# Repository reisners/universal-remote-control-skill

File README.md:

# universal-remote-control-skill

This repository contains resources comprising the Universal Remote Control Alexa Skill

# High-Level Description of the Solution

The system consists of the following components:
* Global components:
  * Alexa Smart Home Skill
  * AWS Lambda function
  * AWS API Gateway websocket endpoint (backed by additional AWS Lambda functions to handle connections)
* Per user-components:
  * Google Account containing a Google Spreadsheet with a fixed name
  * Universal Remote Controller (URC) device based on an ESP8266 micro-controller

The Alexa Smart Home Skill is linked to the user's Google Account in order to access the spreadsheet.
When the user requests device discovery, the skill passes the discovery request on to the AWS Lambda function 
which in turn reads the rows from the spreadsheet and translates them into Alexa Smart Home Device metadata.
Each row contains
* URCID (a unique ID of the URC device derived from an on-board DS2401 chip)
* user-friendly name of the appliance to control, e.g. "Ceiling Fan"
* device category (as prescribed by Alexa Smart Home API)
* operation to perform on that device, e.g. TurnOn/TurnOff
* channel of communication with the appliance (infrared of 433MHz radio waves)
* data package to transmit to the appliance to effect the intended operation

The URC device upon startup creates a websocket connection to the AWS API Gateway via WiFi and passes on its unique URCID.
The AWS Lambda function handling websocket connections stores the combination of URCID and websocket connection ID in an
AWS Dynamo DB table.

When the user requests a device operation via voice command, the skill sends another request to the AWS Lambda function
which refers to the device metadata created during discovery. The AWS Lambda function uses the URCID to find an active
websocket connection ID in the AWS Dynamo DB table, deleting any stale connection IDs it finds. It then sends a message
to the URC device via that websocket connection. This message contains the chosen channel and data package from the Google spreadsheet.

The URC device listens on the open websocket connection for messages and transmits the data to the appliance via infrared or 433MHz radio waves.

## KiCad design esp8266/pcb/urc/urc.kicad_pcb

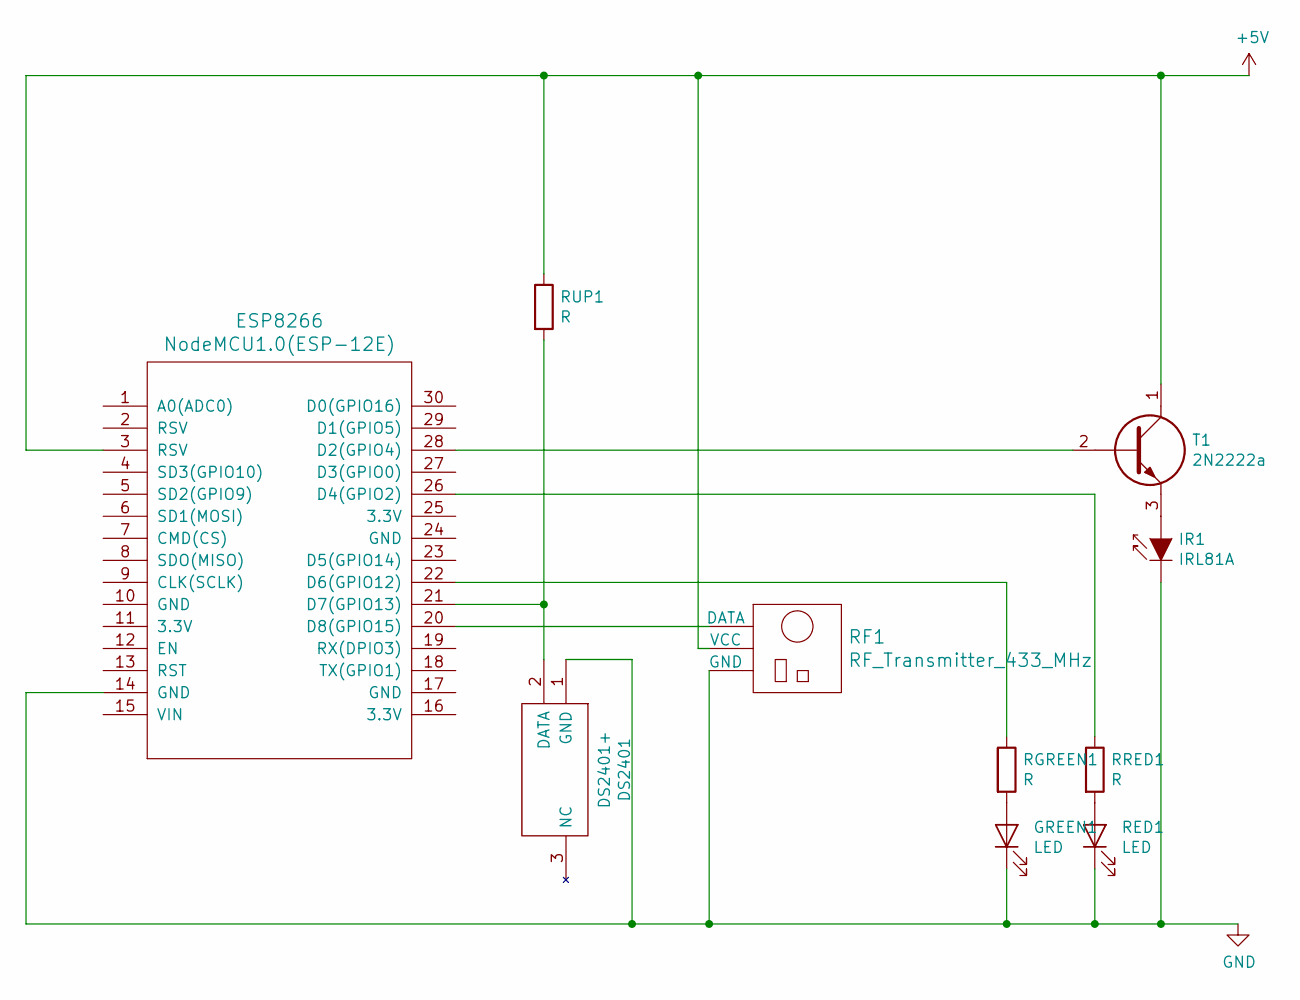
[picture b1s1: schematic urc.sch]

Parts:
DS2401: DS2401+; 2N6027
ESP8266: NodeMCU1.0(ESP-12E); NodeMCU-LoLinV3
GREEN1: LED; LED_D5.0mm
IR1: IRL81A; PinHeader_1x02_P1.00mm_Horizontal
RED1: LED; LED_D5.0mm
RF1: RF_Transmitter_433_MHz
RGREEN1: R; R_Axial_DIN0204_L3.6mm_D1.6mm_P2.54mm_Vertical
RRED1: R; R_Axial_DIN0204_L3.6mm_D1.6mm_P2.54mm_Vertical
RUP1: R; R_Axial_DIN0204_L3.6mm_D1.6mm_P2.54mm_Vertical
T1: 2N2222a; 2N6027

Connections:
+5V: ESP8266.3 (RSV), RF1.2 (VCC), RUP1.1, T1.1
GND: DS2401.1 (GND), ESP8266.14 (GND), GREEN1.1 (K), IR1.1 (K), RED1.1 (K), RF1.3 (GND)
unnamed: DS2401.2 (DATA), ESP8266.21 (D7(GPIO13)), RUP1.2
unnamed: ESP8266.20 (D8(GPIO15)), RF1.1 (DATA)
unnamed: ESP8266.22 (D6(GPIO12)), RGREEN1.1
unnamed: ESP8266.26 (D4(GPIO2)), RRED1.1
unnamed: ESP8266.28 (D2(GPIO4)), T1.2
unnamed: GREEN1.2 (A), RGREEN1.2
unnamed: IR1.2 (A), T1.3
unnamed: RED1.2 (A), RRED1.2

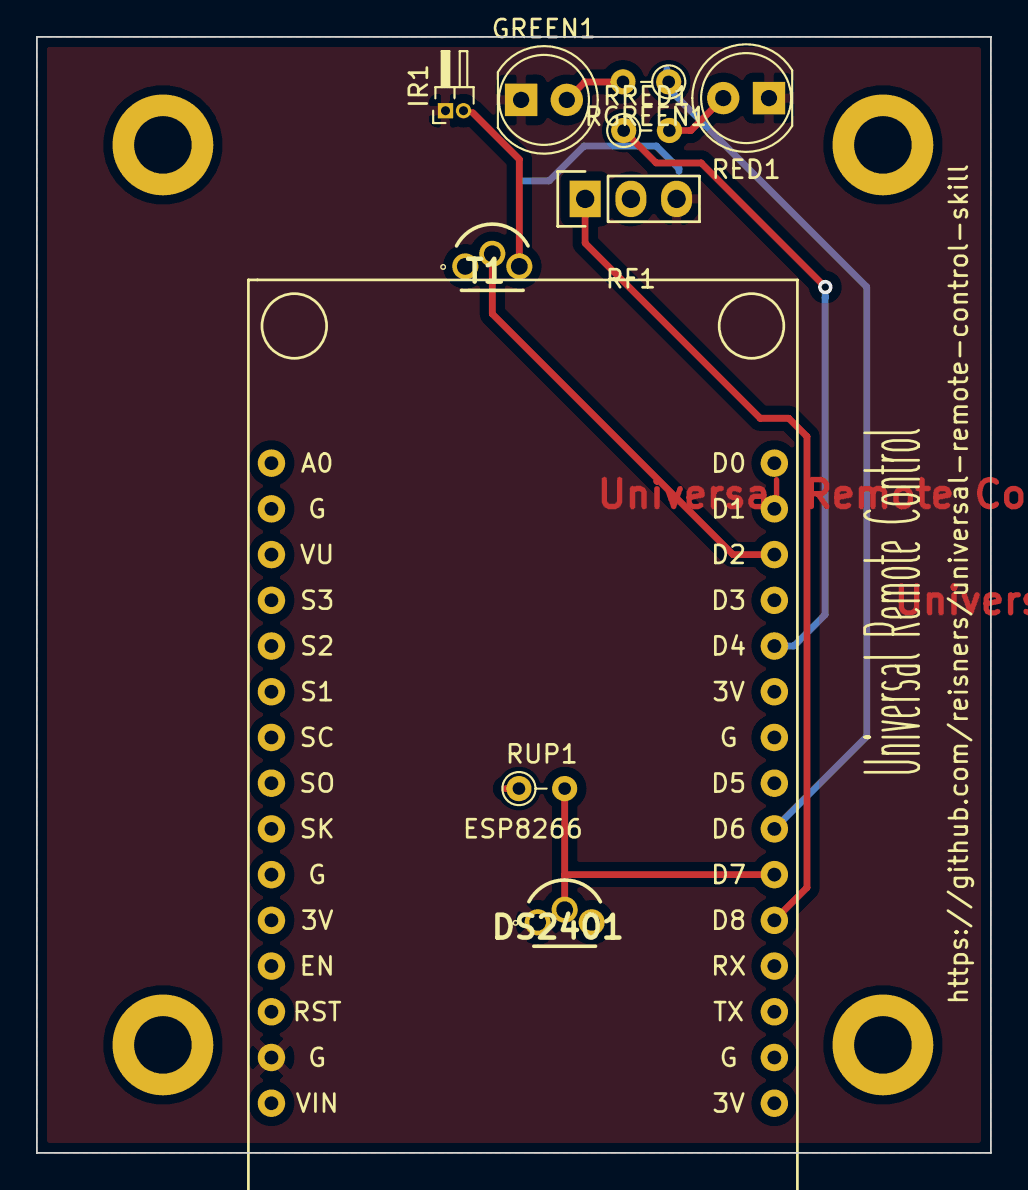
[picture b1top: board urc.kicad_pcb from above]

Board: 2 copper layers, 53.0 x 62.0 mm, 10 parts (0 on the bottom side), 10 nets.

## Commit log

2019-04-21 adr initialized
2019-08-27 renamed universion-remote-control-smart-home-skill (from universal-remote-control), added claudia.json, package-lock.json
2019-08-30 documentation updated
2019-08-30 image1.jpg added
2019-08-30 renamed esp8266/urc
2019-10-15 updated urc.ino: adding status LEDs
2019-10-20 updated lambda/universal-remote-control-smart-home-skill/index.js
2019-11-07 added emulator
2019-11-10 updated emulator.js
2019-11-10 updated urc.ino
2019-12-05 updated index.js: improving discovery error handling
2019-12-05 added esp8266/pcb
2020-06-08 updated index.js: logging
2020-06-08 updated urc.ino: improved LED signaling
2020-09-02 Bump googleapis in /lambda/universal-remote-control-smart-home-skill
    Bumps [googleapis](https://github.com/googleapis/google-api-nodejs-client) from 35.0.0 to 39.1.0.
    - [Release notes](https://github.com/googleapis/google-api-nodejs-client/releases)
    - [Changelog](https://github.com/googleapis/google-api-nodejs-client/blob/master/CHANGELOG.md)
    - [Commits](https://github.com/googleapis/google-api-nodejs-client/compare/v35.0.0...v39.1.0)
2020-10-17 added icon_*.png
2020-10-17 added ir_captures/*
2021-04-02 updated urc.ino: adding support for WakeOnLan
2021-04-02 added urc.code-workspace
2021-11-16 Bump aws-sdk in /lambda/universal-remote-control-smart-home-skill
    Bumps [aws-sdk](https://github.com/aws/aws-sdk-js) from 2.517.0 to 2.814.0.
    - [Release notes](https://github.com/aws/aws-sdk-js/releases)
    - [Changelog](https://github.com/aws/aws-sdk-js/blob/master/CHANGELOG.md)
    - [Commits](https://github.com/aws/aws-sdk-js/compare/v2.517.0...v2.814.0)
    ---
    updated-dependencies:
2022-02-07 adapting to newer version of ArduinoJson
2022-02-07 ignored
2022-02-07 schematics exported
2022-02-07 checking in urc-cache.lib
2022-02-07 committing changes
2024-12-29 added parameters nrepeat and delay to WakeOnLan channel
